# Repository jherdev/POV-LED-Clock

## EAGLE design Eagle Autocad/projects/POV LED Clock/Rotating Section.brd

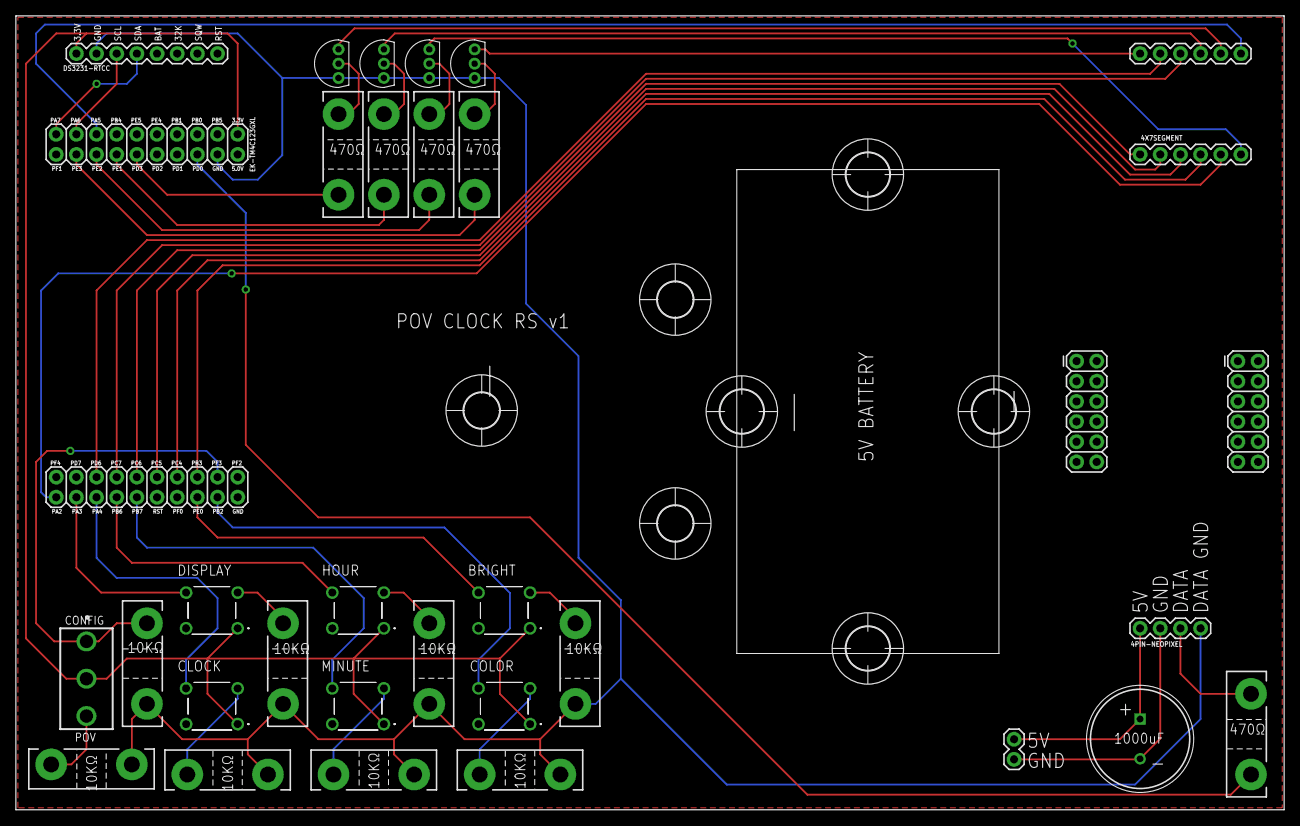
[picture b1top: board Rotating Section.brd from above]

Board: 2 copper layers, 159.7 x 100.0 mm, 39 parts (0 on the bottom side), 42 nets.

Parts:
BRIGHT: PTS645SL432LFS
C1: 1000uF; CAPPRD500W65D1250H2200
CLOCK: PTS645SL432LFS
COLOR: PTS645SL432LFS
DISPLAY: PTS645SL432LFS
E$1: LEDPANEL
E$2: 5VBATTERY
E$3, E$11, E$12, E$13: 5,5
E$8, E$9, E$10: 4,5
HOUR: PTS645SL432LFS
MINUTE: PTS645SL432LFS
Q1, Q2, Q3, Q4: P2N2222AG; TO-92
R1, R2, R3, R4, R5, R6, R7, R8: 10KΩ; TO-247-2V
R9, R10, R11, R12, R13: 470Ω; TO-247-2V
S1: 1101M2S3CQE2; 1000-SERIES(SPDT)
U$1: 4X7SEGMENT
U$2: DS3231-RTCC; 1X08
U$3: EK-TM4C123GXL
U$4: 4PIN-NEOPIXEL
U$5: 2PIN-BATTERY

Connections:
3.3V: BRIGHT.1, CLOCK.1, COLOR.1, DISPLAY.1, HOUR.1, MINUTE.1, S1.2, U$2.1, U$3.1
DATA: R13.1, U$3.6
GND: Q1.1, Q2.1, Q3.1, Q4.1, R1.1, R2.1, R3.2, R4.2, R5.2, R6.2, R7.2, R8.2, U$2.2, U$3.4, U$4.4
unnamed: U$2.3, U$3.17
unnamed: U$2.4, U$3.19
unnamed: R2.2, S1.3
unnamed: COLOR.4, U$3.24
unnamed: R1.2, S1.1, U$3.23
unnamed: BRIGHT.4, U$3.26
unnamed: MINUTE.4, U$3.32
unnamed: HOUR.4, U$3.34
unnamed: CLOCK.4, U$3.36
unnamed: DISPLAY.4, U$3.38
unnamed: COLOR.3, R3.1
unnamed: BRIGHT.3, R4.1
unnamed: MINUTE.3, R5.1
unnamed: HOUR.3, R6.1
unnamed: CLOCK.3, R7.1
unnamed: DISPLAY.3, R8.1
unnamed: R9.2, U$3.18
unnamed: Q1.2, R9.1
unnamed: R11.2, U$3.12
unnamed: Q1.3, U$1.12
unnamed: U$1.10, U$3.33
unnamed: U$1.11, U$3.35
unnamed: R10.2, U$3.14
unnamed: U$1.1, U$3.31
unnamed: U$1.2, U$3.29
unnamed: U$1.3, U$3.27
unnamed: U$1.4, U$3.25
unnamed: U$1.5, U$3.40
unnamed: U$1.7, U$3.15
unnamed: Q4.2, R10.1
unnamed: Q3.2, R11.1
unnamed: R12.2, U$3.16
unnamed: Q4.3, U$1.9
unnamed: Q3.3, U$1.8
unnamed: Q2.2, R12.1
unnamed: Q2.3, U$1.6
unnamed: R13.2, U$4.3
unnamed: C1.1, U$4.1, U$5.1
unnamed: C1.2, U$4.2, U$5.2

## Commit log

2019-07-03 Initial commit, corrected button polling
2019-07-03 misc updates - git testing
2019-07-03 updating commit files
2019-07-03 git staging continued
2019-07-03 git setup complete?
2019-07-10 Added setup for four digit 7-segment
2019-07-16 Added color toggle button
2019-07-19 4 digit 7 segment working, segment A not working
2019-07-19 sseg functions written & working
2019-07-24 updated button pins for easier schematic/pcb connections
2019-07-28 updated pin to match changes in PCB design
2019-07-30 pin swapped PF3 and PA2, hour configuration continues to be buggy
2019-08-01 added PCB design and custom library files
2019-08-02 integrated 7 segment display to button interface
2019-08-05 seperated seven segment and rtcc functions to seperate files
2019-08-06 added misc header and source files, contains bcd conversion and decoding functions as well as timed delay functions. adjust_brightness function is now performed during config instead of every time se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
2019-08-06 moved led function to seperate source files, updated various button functions
2019-08-24 misc
2019-08-26 added baseline for Hall Effect Sensor GPIO rising edge interrupt
2019-09-14 build falling edge hall effect sensor interrupt - untested
2019-09-14 added interrupts header and source files, successfully tested interrupt setup and ISR
2019-09-15 began work of developing hall effect sensor falling edge ISR
2019-09-15 successfully POV displayed character '8'
2019-09-16 added rudimentary 5 degree representations of 0 through 9
2019-09-18 synced motorv1 to an appropriate pwm, modified led_map values
2019-09-18 Refined PWM control and display
2019-09-18 developed 12 hour display for interrupt, untested
2019-09-19 updated 12-hour segment of interrupt, developed basic layout for Hand Clock segment of interrupt
2019-09-19 modifed values on led_map.h
2019-09-21 12/24 hour display working, HC still needs work on algorithm
2019-09-23 incorporated switch to toggle motor to motorv1 system project
2019-09-23 continued development of Hand Clock display
2019-10-05 misc changes for documentation purposes
2019-11-01 Added LightColumn function, changed syntax for several function names
2019-11-22 latest updates, worked in with documentation
2019-12-04 Cleaned up commented code, no longer necessary
2019-12-06 updated POV Hand Clock case of ISR
